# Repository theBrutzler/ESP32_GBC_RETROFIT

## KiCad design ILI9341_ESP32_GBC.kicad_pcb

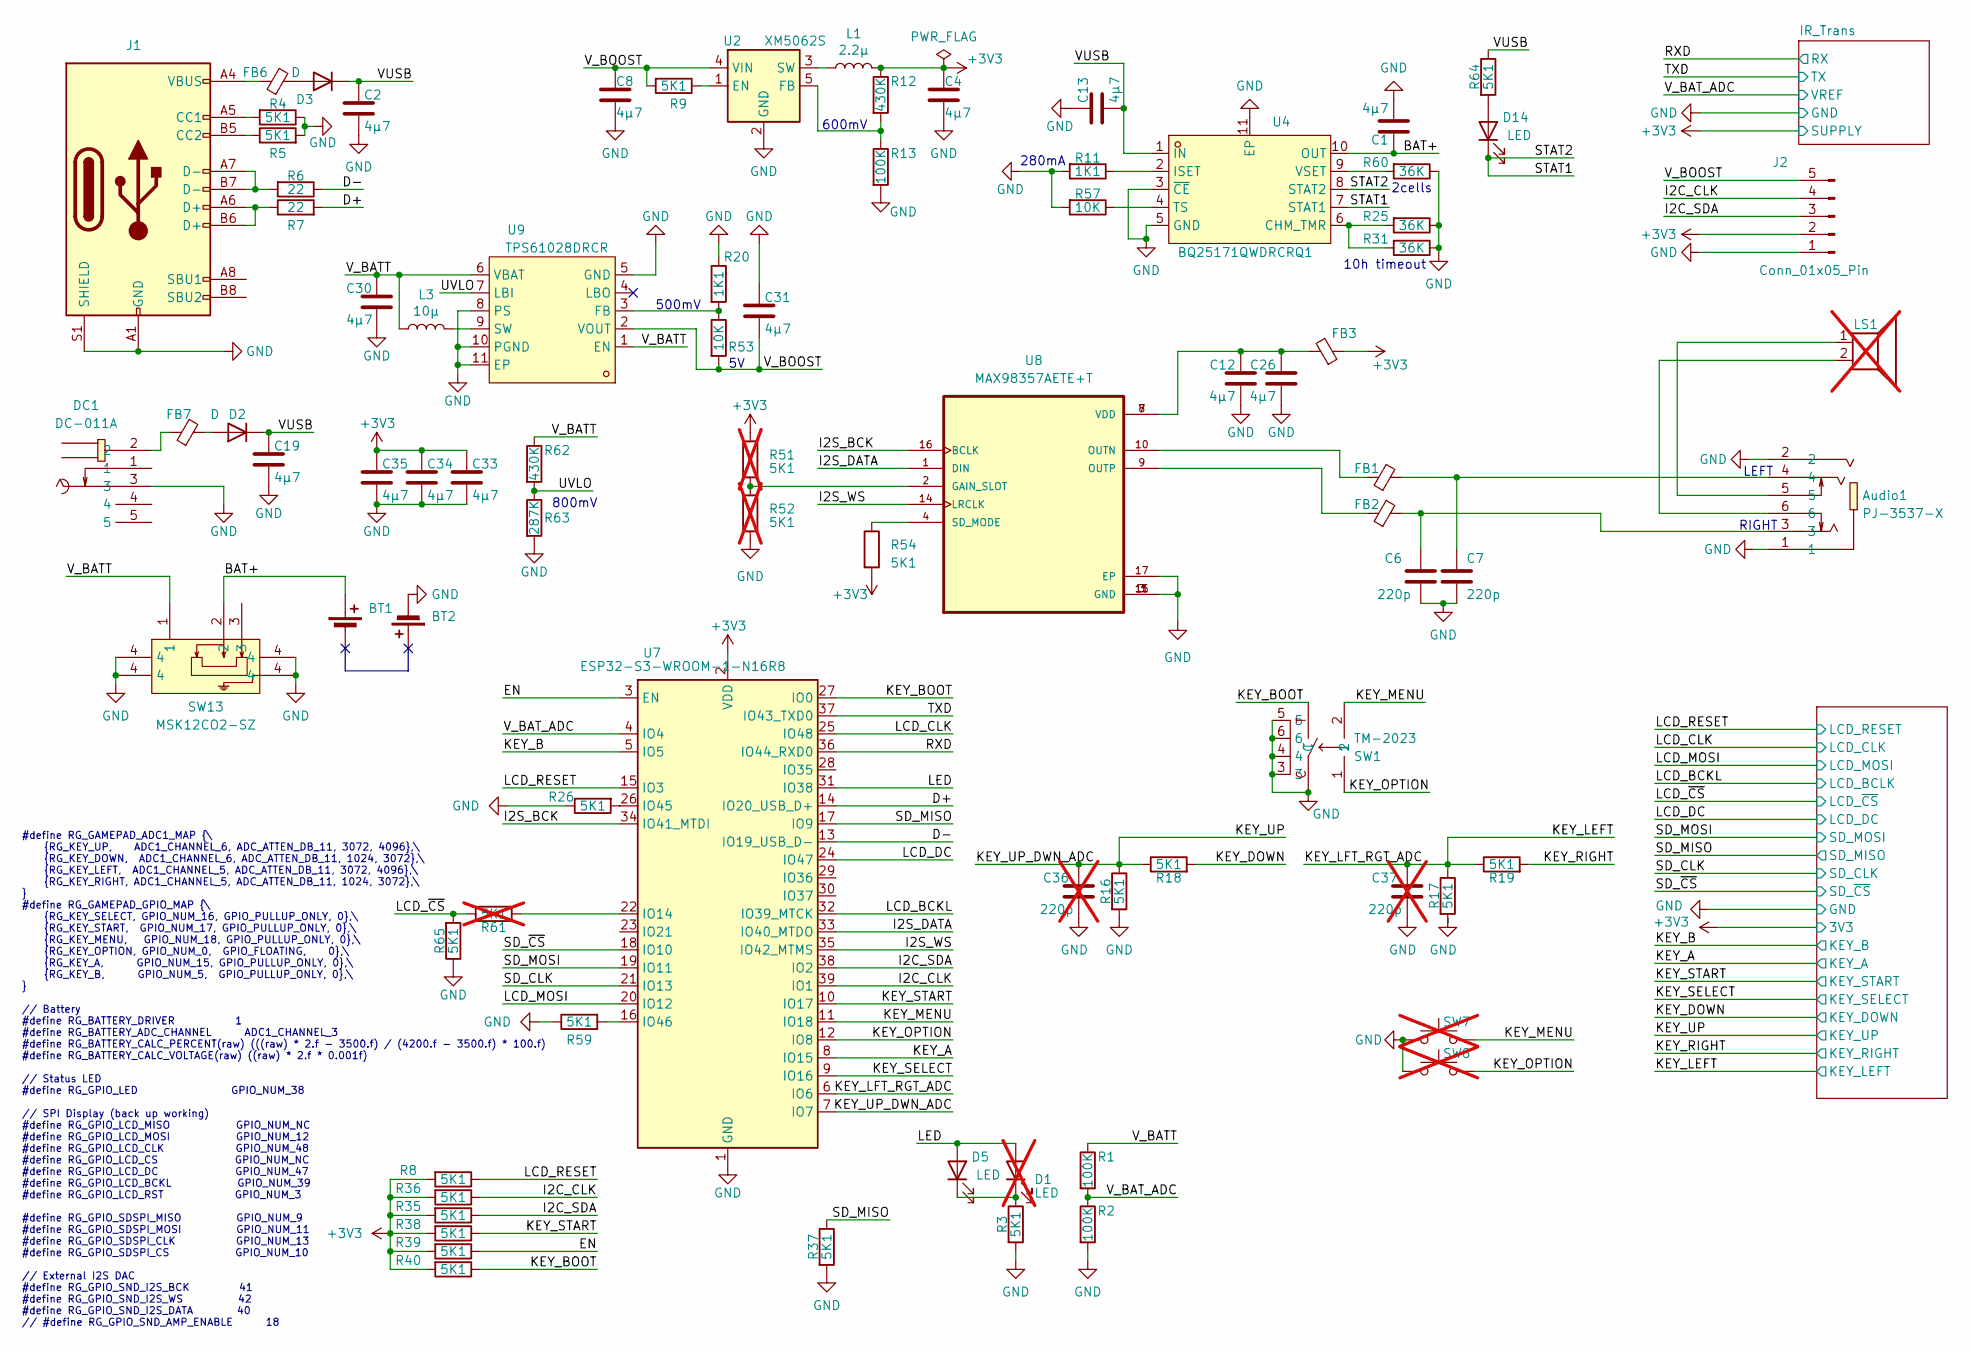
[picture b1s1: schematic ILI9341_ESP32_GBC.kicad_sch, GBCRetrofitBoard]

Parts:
Audio1: PJ-3537-X; AUDIO-SMD_PJ-3420-A-SMT_C319102; LCSC Part C319102
BT1: Battery_Cell; CONN-SMD_MY-ZJ-3030; LCSC C964874
BT2: Battery_Cell; BAT-SMD_MY-FJ-3031; LCSC C964876
C1, C2, C4, C8, C12, C13, C19, C26, C30, C31, C33, C34, C35: 4µ7; C_0603_1608Metric; LCSC C69335
C6, C7: 220p; C_0603_1608Metric; LCSC C107081
C36, C37: 220p; C_0603_1608Metric; LCSC C107081; not fitted
D1: LED; LED_D3.0mm_FlatTop; LCSC C440523; not fitted
D2, D3: D; Nexperia_CFP3_SOD-123W; LCSC C5120763
D5, D14: LED; LED_0603_1608Metric; LCSC C7496818
DC1: DC-011A; DC-IN-TH_DC-011A; LCSC Part C480366
FB1, FB2, FB3, FB6, FB7: FerriteBead_Small; L_0805_2012Metric; LCSC C963878
J1: USB_C_Receptacle_USB2.0_16P; USB_C_Receptacle_HRO_TYPE-C-31-M-12; LCSC C165948
J2: Conn_01x05_Pin; PinHeader_1x05_P2.54mm_Vertical
L1: 2.2µ; L_1210_3225Metric_Pad1.42x2.65mm_HandSolder; LCSC C3002559
L3: 10µ; L_1210_3225Metric_Pad1.42x2.65mm_HandSolder; LCSC C39846645
LS1: Speaker; PinHeader_1x02_P2.54mm_Vertical; LCSC C391015; not fitted
R1, R2, R13: 100K; R_0603_1608Metric; LCSC C15458
R3, R4, R5, R8, R9, R16, R17, R18, R19, R26, R35, R36, R37, R38, R39, R40, R54, R59, R64, R65: 5K1; R_0603_1608Metric; LCSC C26000
R6, R7: 22; R_0603_1608Metric; LCSC C1203
R11, R20: 1K1; R_0603_1608Metric; LCSC C2906975
R12, R62: 430K; R_0603_1608Metric; LCSC C25969
R25, R31, R60: 36K; R_0603_1608Metric; LCSC C23147
R51, R52, R61: 5K1; R_0603_1608Metric; LCSC C26000; not fitted
R53, R57: 10K; R_0603_1608Metric; LCSC C25804
R63: 287K; R_0603_1608Metric; LCSC C22972
SW1: TM-2023; SW-SMD_TM-2023-1; LCSC C318951
SW7, SW8: SW_Push; RubberpadButton_250µ_250µ; not fitted
SW13: MSK12CO2-SZ; SW-TH_MSK12C02; LCSC C2681568
U2: XM5062S; SOT-23-5; LCSC C2924930
U4: BQ25171QWDRCRQ1; VSON-10_L3.0-W3.0-P0.50-BL-EP1.65; LCSC Part C2861221
U7: ESP32-S3-WROOM-1-N16R8; ESP32-S3-WROOM-1; LCSC C2913202
U8: MAX98357AETE+T; QFN-16-1EP_3x3mm_P0.5mm_EP1.45x1.45mm; LCSC C910544
U9: TPS61028DRCR; VSON-10_L3.0-W3.0-P0.50-TL-EP-1; LCSC Part C575574

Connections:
+3V3: C4.1, C33.1, C34.1, C35.1, FB3.1, J2.2, L1.2, R8.2, R12.1, R35.2, R36.2, R38.2, R39.2, R40.2, R51.1, R54.2, U7.2 (VDD); also elsewhere on the board
/BAT+: BT1.1 (+), C1.1, SW13.2, U4.10 (OUT)
/D+: R7.2, U7.14 (IO20_USB_D+)
/D-: R6.1, U7.13 (IO19_USB_D-)
/EN: R39.1, U7.3 (EN)
/I2C_CLK: J2.4, R36.1, U7.39 (IO1)
/I2C_SDA: J2.3, R35.1, U7.38 (IO2)
/I2S_BCK: U7.34 (IO41_MTDI), U8.16 (BCLK)
/I2S_DATA: U7.33 (IO40_MTDO), U8.1 (DIN)
/I2S_WS: U7.35 (IO42_MTMS), U8.14 (LRCLK)
/KEY_A: U7.8 (IO15); also elsewhere on the board
/KEY_B: U7.5 (IO5); also elsewhere on the board
/KEY_BOOT: R40.1, SW1.T, U7.27 (IO0)
/KEY_DOWN: R18.2; also elsewhere on the board
/KEY_LEFT: C37.1, R17.1, R19.1, U7.6 (IO6); also elsewhere on the board
/KEY_MENU: SW1.2, SW7.2, U7.11 (IO18)
/KEY_OPTION: SW1.1, SW8.2, U7.12 (IO8)
/KEY_RIGHT: R19.2; also elsewhere on the board
/KEY_SELECT: U7.9 (IO16); also elsewhere on the board
/KEY_START: R38.1, U7.10 (IO17); also elsewhere on the board
/KEY_UP: C36.1, R16.1, R18.1, U7.7 (IO7); also elsewhere on the board
/LCD_BCKL: U7.32 (IO39_MTCK); also elsewhere on the board
/LCD_CLK: U7.25 (IO48); also elsewhere on the board
/LCD_DC: U7.24 (IO47); also elsewhere on the board
/LCD_MOSI: U7.20 (IO12); also elsewhere on the board
/LCD_RESET: R8.1, U7.15 (IO3); also elsewhere on the board
/LCD_~CS: R61.2, R65.2; also elsewhere on the board
/LED: D1.2 (A), D5.2 (A), U7.31 (IO38)
/RXD: U7.36 (IO44_RXD0); also elsewhere on the board
/SD_CLK: U7.21 (IO13); also elsewhere on the board
/SD_MISO: R37.1, U7.17 (IO9); also elsewhere on the board
/SD_MOSI: U7.19 (IO11); also elsewhere on the board
/SD_~CS: U7.18 (IO10); also elsewhere on the board
/STAT1: D14.1 (K), U4.7 (STAT1), U4.8 (STAT2)
/TXD: U7.37 (IO43_TXD0); also elsewhere on the board
/UVLO: R62.2, R63.1, U9.7 (LBI)
/VUSB: C2.1, C13.2, C19.1, D2.1 (K), D3.1 (K), R64.1, U4.1 (IN)
/V_BATT: C30.1, L3.1, R1.1, R62.1, SW13.1, U9.1 (EN), U9.6 (VBAT)
/V_BAT_ADC: R1.2, R2.1, U7.4 (IO4); also elsewhere on the board
/V_BOOST: C8.1, C31.2, J2.5, R9.2, R53.2, U2.4 (VIN), U9.2 (VOUT)
GND: Audio1.1, Audio1.2, BT2.2 (-), C1.2, C2.2, C4.2, C6.2, C7.1, C8.2, C12.2, C13.1, C19.2, C26.2, C30.2, C31.1, C33.2, C34.2, C35.2, C36.2, C37.2, DC1.3, J1.A1 (GND), J1.A12 (GND), J1.B1 (GND), J1.B12 (GND), J1.S1 (SHIELD), J2.1, R2.2, R3.2, R4.1, R5.2, R11.2, R13.2, R16.2, R17.2, R20.1, R25.1, R26.1, R31.1, R37.2, R52.2, R57.2, R59.1, R60.1, R63.2, R65.1, SW1.3, SW1.4, SW1.5, SW1.6, SW1.C, SW7.1, SW8.1, SW13.4, U2.2 (GND), U4.3 (~CE), U4.5 (GND), U4.11 (EP), U7.1 (GND), U7.40 (GND), U7.41 (GND), U8.3 (GND), U8.11 (GND), U8.15 (GND), U8.17 (EP), U9.5 (GND), U9.8 (PS), U9.10 (PGND), U9.11 (EP); also elsewhere on the board
unnamed: Audio1.3, C6.1, FB2.2
unnamed: Audio1.4, C7.2, FB1.2
unnamed: Audio1.5, LS1.1
unnamed: Audio1.6, LS1.2
unnamed: C12.1, C26.1, FB3.2, U8.7 (VDD), U8.8 (VDD)
unnamed: D1.1 (K), D5.1 (K), R3.1
unnamed: D2.2 (A), FB7.2
unnamed: D3.2 (A), FB6.2
unnamed: D14.2 (A), R64.2
unnamed: DC1.2, FB7.1
unnamed: FB6.1, J1.A4 (VBUS), J1.A9 (VBUS), J1.B4 (VBUS), J1.B9 (VBUS)
unnamed: J1.A5 (CC1), R4.2
unnamed: J1.B5 (CC2), R5.1
unnamed: J1.A6 (D+), J1.B6 (D+), R7.1
unnamed: J1.A7 (D-), J1.B7 (D-), R6.2
unnamed: R9.1, U2.1 (EN)
unnamed: R12.2, R13.1, U2.5 (FB)
unnamed: L1.1, U2.3 (SW)
unnamed: R25.2, R31.2, U4.6 (CHM_TMR)
unnamed: R11.1, U4.2 (ISET)
unnamed: R57.1, U4.4 (TS)
unnamed: R60.2, U4.9 (VSET)
unnamed: R61.1, U7.22 (IO14)
unnamed: R26.2, U7.26 (IO45)
unnamed: R59.2, U7.16 (IO46)
unnamed: R51.2, R52.1, U8.2 (GAIN_SLOT)
unnamed: FB1.1, U8.10 (OUTN)
unnamed: FB2.1, U8.9 (OUTP)
unnamed: R54.1, U8.4 (SD_MODE)
unnamed: R20.2, R53.1, U9.3 (FB)
unnamed: L3.2, U9.9 (SW)

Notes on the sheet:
RIGHT
500mV
600mV
280mA
2cells
LEFT
800mV
#define RG_GAMEPAD_ADC1_MAP {\ {RG_KEY_UP, ADC1_CHANNEL_6, ADC_ATTEN_DB_11, 3072, 4096},\ {RG_KEY_DOWN, ADC1_CHANNEL_6, ADC_ATTEN_DB_11, 1024, 3072},\ {RG_KEY_LEFT, ADC1_CHANNEL_5, ADC_ATTEN_DB_11, 3072, 4096},\ {RG_KEY_RIGHT, ADC1_CHANNEL_5, ADC_ATTEN_DB_11, 1024, 3072},\ } #define RG_GAMEPAD_GPIO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
10h timeout

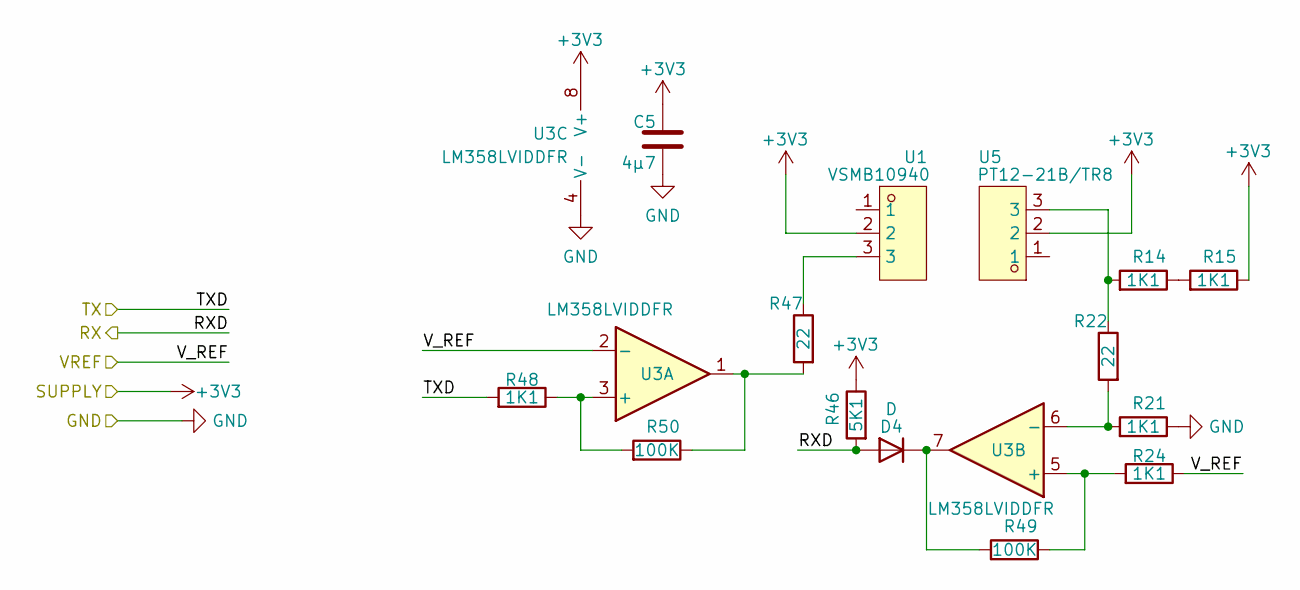
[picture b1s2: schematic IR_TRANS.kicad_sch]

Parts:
C5: 4µ7; C_0603_1608Metric; LCSC C69335
D4: D; Nexperia_CFP3_SOD-123W; LCSC C5120763
R14, R15, R21, R24, R48: 1K1; R_0603_1608Metric; LCSC C2906975
R22, R47: 22; R_0603_1608Metric; LCSC C1203
R46: 5K1; R_0603_1608Metric; LCSC C26000
R49, R50: 100K; R_0603_1608Metric; LCSC C15458
U1: VSMB10940; LED-SMD_3P-L3.0-W1.0-FD; LCSC Part C4749241
U3: LM358LVIDDFR; TSOT-23-8; LCSC C1849428
U5: PT12-21B/TR8; LED-SMD_3P-L3.0-W1.0-FD; LCSC C264383

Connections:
+3V3: C5.1, R15.1, R46.1, U1.2, U3.8 (V+), U5.2; also elsewhere on the board
/RXD: D4.2 (A), R46.2; also elsewhere on the board
/TXD: R48.2; also elsewhere on the board
/V_BAT_ADC: R24.1, U3.2 (-); also elsewhere on the board
GND: C5.2, R21.1, U3.4 (V-); also elsewhere on the board
unnamed: D4.1 (K), R49.2, U3.7
unnamed: R14.1, R15.2
unnamed: R14.2, R22.1, U5.3
unnamed: R47.1, U1.3
unnamed: R47.2, R50.1, U3.1
unnamed: R48.1, R50.2, U3.3 (+)
unnamed: R24.2, R49.1, U3.5 (+)
unnamed: R21.2, R22.2, U3.6 (-)

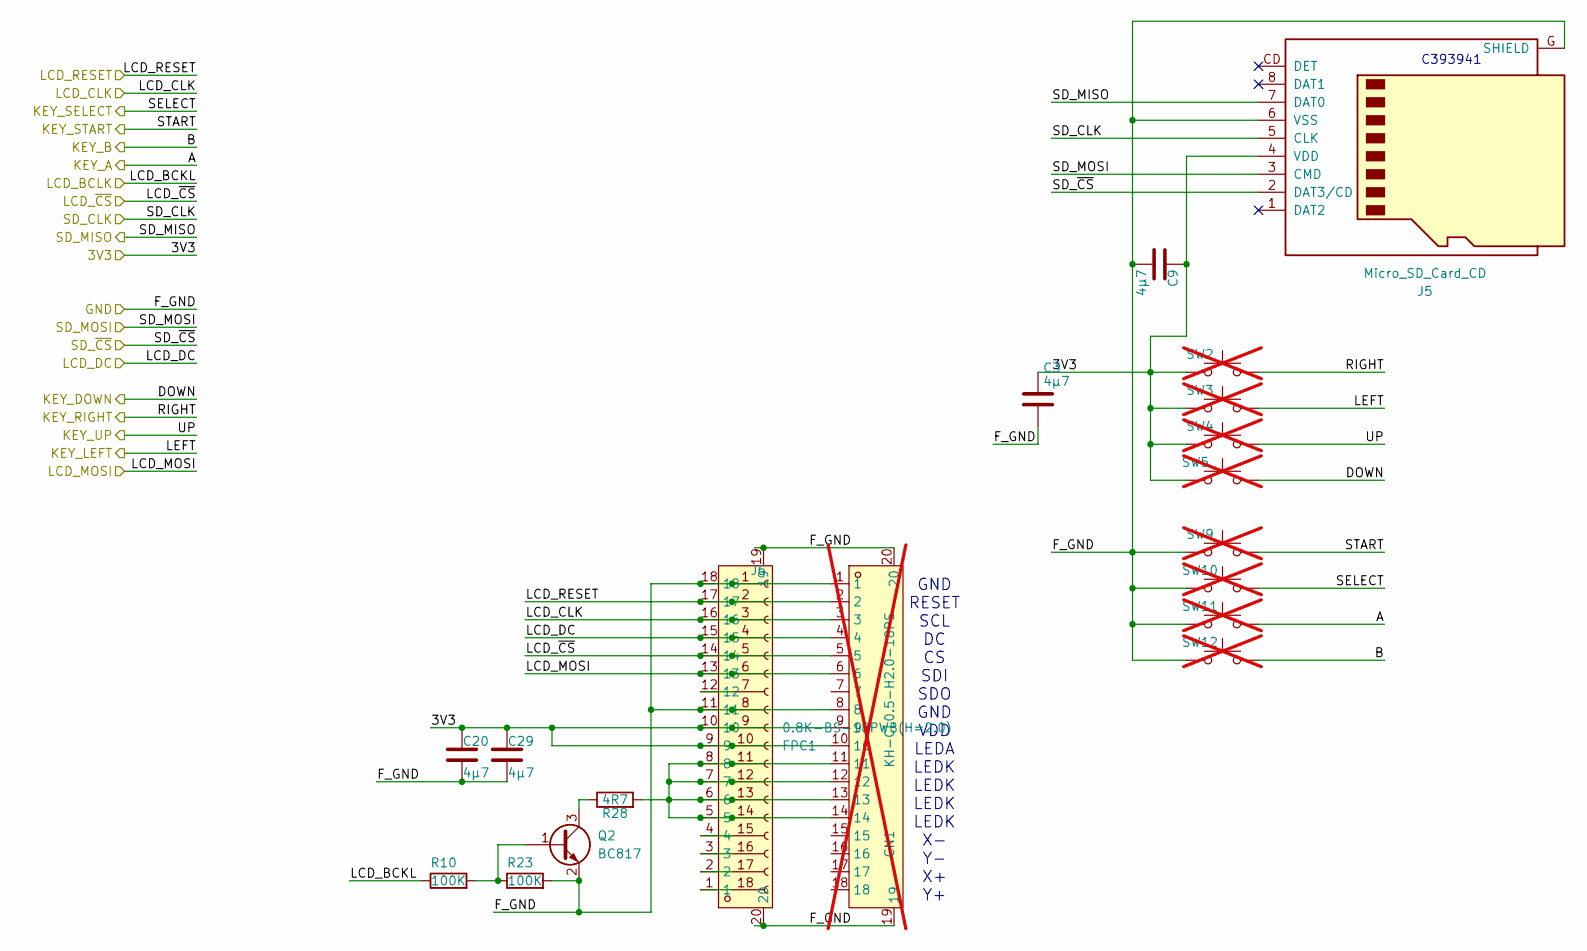
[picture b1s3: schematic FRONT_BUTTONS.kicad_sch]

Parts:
C3, C9, C20, C29: 4µ7; C_0603_1608Metric; LCSC C69335
CN1: KH-CL0.5-H2.0-18PS; FPC-SMD_KH-CL0.5-H2.0-18PS; LCSC Part C2828051; not fitted
FPC1: 0.8K-BS-18PWB(H=2.0); FPC-SMD_18P-P0.80_HDGC_0.8K-BS-18PWB; LCSC Part C2915417
J5: Micro_SD_Card_CD; MicroSD_Self_ bomb; LCSC C393941
J6: Conn_01x18_Socket; solder connector 0.8mm 18 pin
Q2: BC817; SOT-323_SC-70; LCSC C605312
R10, R23: 100K; R_0603_1608Metric; LCSC C15458
R28: 4R7; R_0603_1608Metric; LCSC C491192
SW2, SW3, SW4, SW5: SW_Push; RubberpadButton_GBC_CROSS; not fitted
SW9, SW10, SW11, SW12: SW_Push; RubberpadButton_250µ_250µ; not fitted

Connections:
+3V3: C3.1, C9.1, C20.1, C29.1, CN1.9, CN1.10, FPC1.9, FPC1.10, J5.4 (VDD), J6.9, J6.10, SW2.1, SW3.1, SW4.1, SW5.2; also elsewhere on the board
/KEY_A: SW11.2; also elsewhere on the board
/KEY_B: SW12.2; also elsewhere on the board
/KEY_DOWN: SW5.1; also elsewhere on the board
/KEY_LEFT: SW3.2; also elsewhere on the board
/KEY_RIGHT: SW2.2; also elsewhere on the board
/KEY_SELECT: SW10.2; also elsewhere on the board
/KEY_START: SW9.2; also elsewhere on the board
/KEY_UP: SW4.2; also elsewhere on the board
/LCD_BCKL: R10.1; also elsewhere on the board
/LCD_CLK: CN1.3, FPC1.16, J6.3; also elsewhere on the board
/LCD_DC: CN1.4, FPC1.15, J6.4; also elsewhere on the board
/LCD_MOSI: CN1.6, FPC1.13, J6.6; also elsewhere on the board
/LCD_RESET: CN1.2, FPC1.17, J6.2; also elsewhere on the board
/LCD_~CS: CN1.5, FPC1.14, J6.5; also elsewhere on the board
/SD_CLK: J5.5 (CLK); also elsewhere on the board
/SD_MISO: J5.7 (DAT0); also elsewhere on the board
/SD_MOSI: J5.3 (CMD); also elsewhere on the board
/SD_~CS: J5.2 (DAT3/CD); also elsewhere on the board
GND: C3.2, C9.2, C20.2, C29.2, CN1.1, CN1.8, CN1.19, CN1.20, FPC1.11, FPC1.18, FPC1.19, FPC1.20, J5.6 (VSS), J5.G (SHIELD), J6.1, J6.8, Q2.2 (E), R23.2, SW9.1, SW10.1, SW11.1, SW12.1; also elsewhere on the board
unnamed: FPC1.12, J6.7
unnamed: CN1.11, CN1.12, CN1.13, CN1.14, FPC1.5, FPC1.6, FPC1.7, FPC1.8, J6.11, J6.12, J6.13, J6.14, R28.2
unnamed: FPC1.4, J6.15
unnamed: FPC1.3, J6.16
unnamed: FPC1.2, J6.17
unnamed: FPC1.1, J6.18
unnamed: Q2.1 (B), R10.2, R23.1
unnamed: Q2.3 (C), R28.1

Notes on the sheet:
GND RESET SCL DC CS SDI SDO GND VDD LEDA LEDK LEDK LEDK LEDK X- Y- X+ Y+
C393941

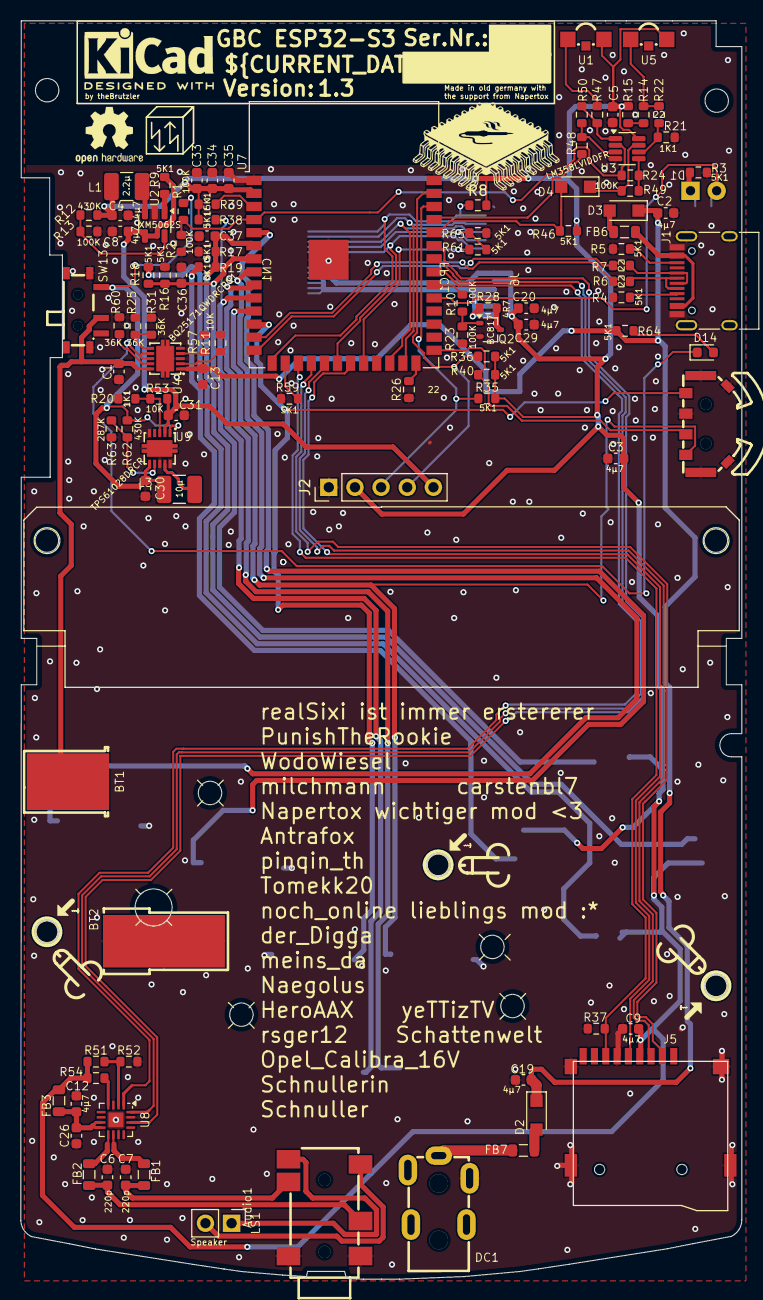
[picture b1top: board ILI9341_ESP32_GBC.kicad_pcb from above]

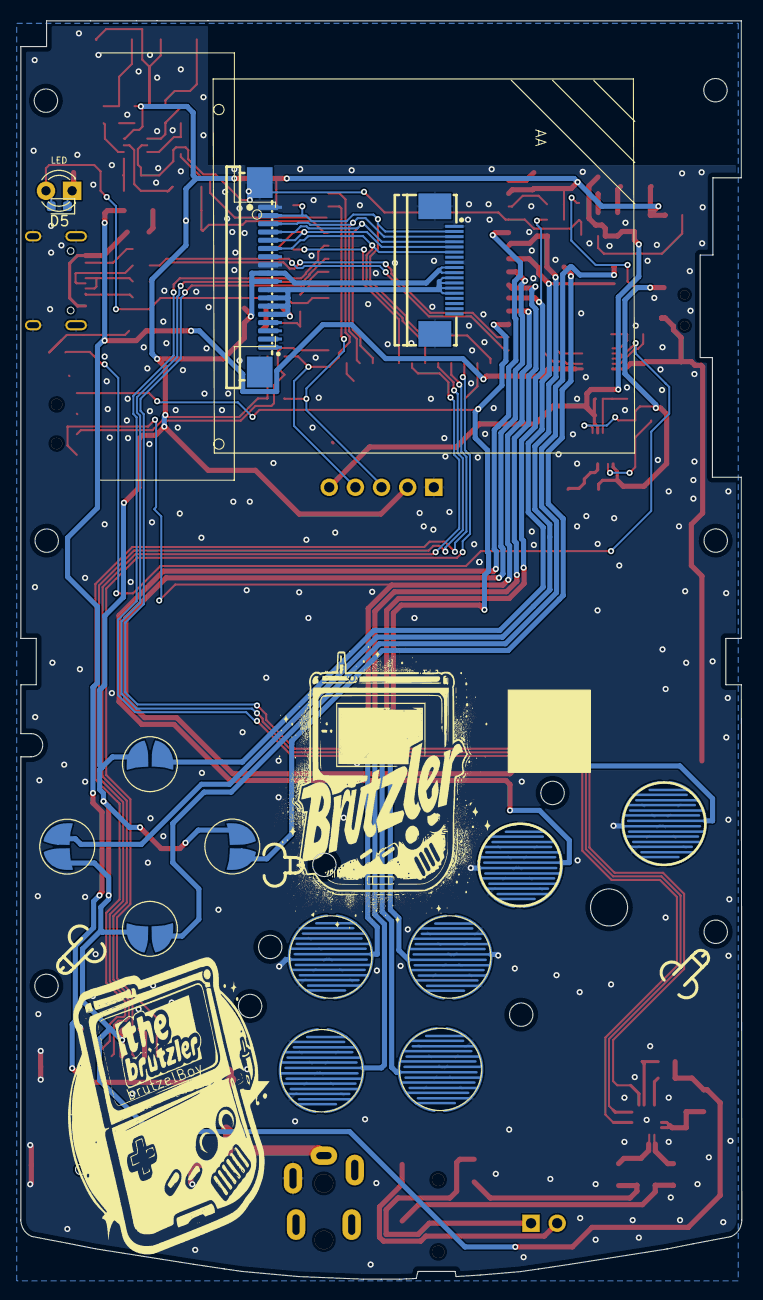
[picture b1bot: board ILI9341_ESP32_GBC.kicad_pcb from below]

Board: 2 copper layers, 70.0 x 122.2 mm, 119 parts (15 on the bottom side), 88 nets.

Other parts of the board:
SM3: SYM_Arrow45_Tiny; Symbol_kurzschlussblog

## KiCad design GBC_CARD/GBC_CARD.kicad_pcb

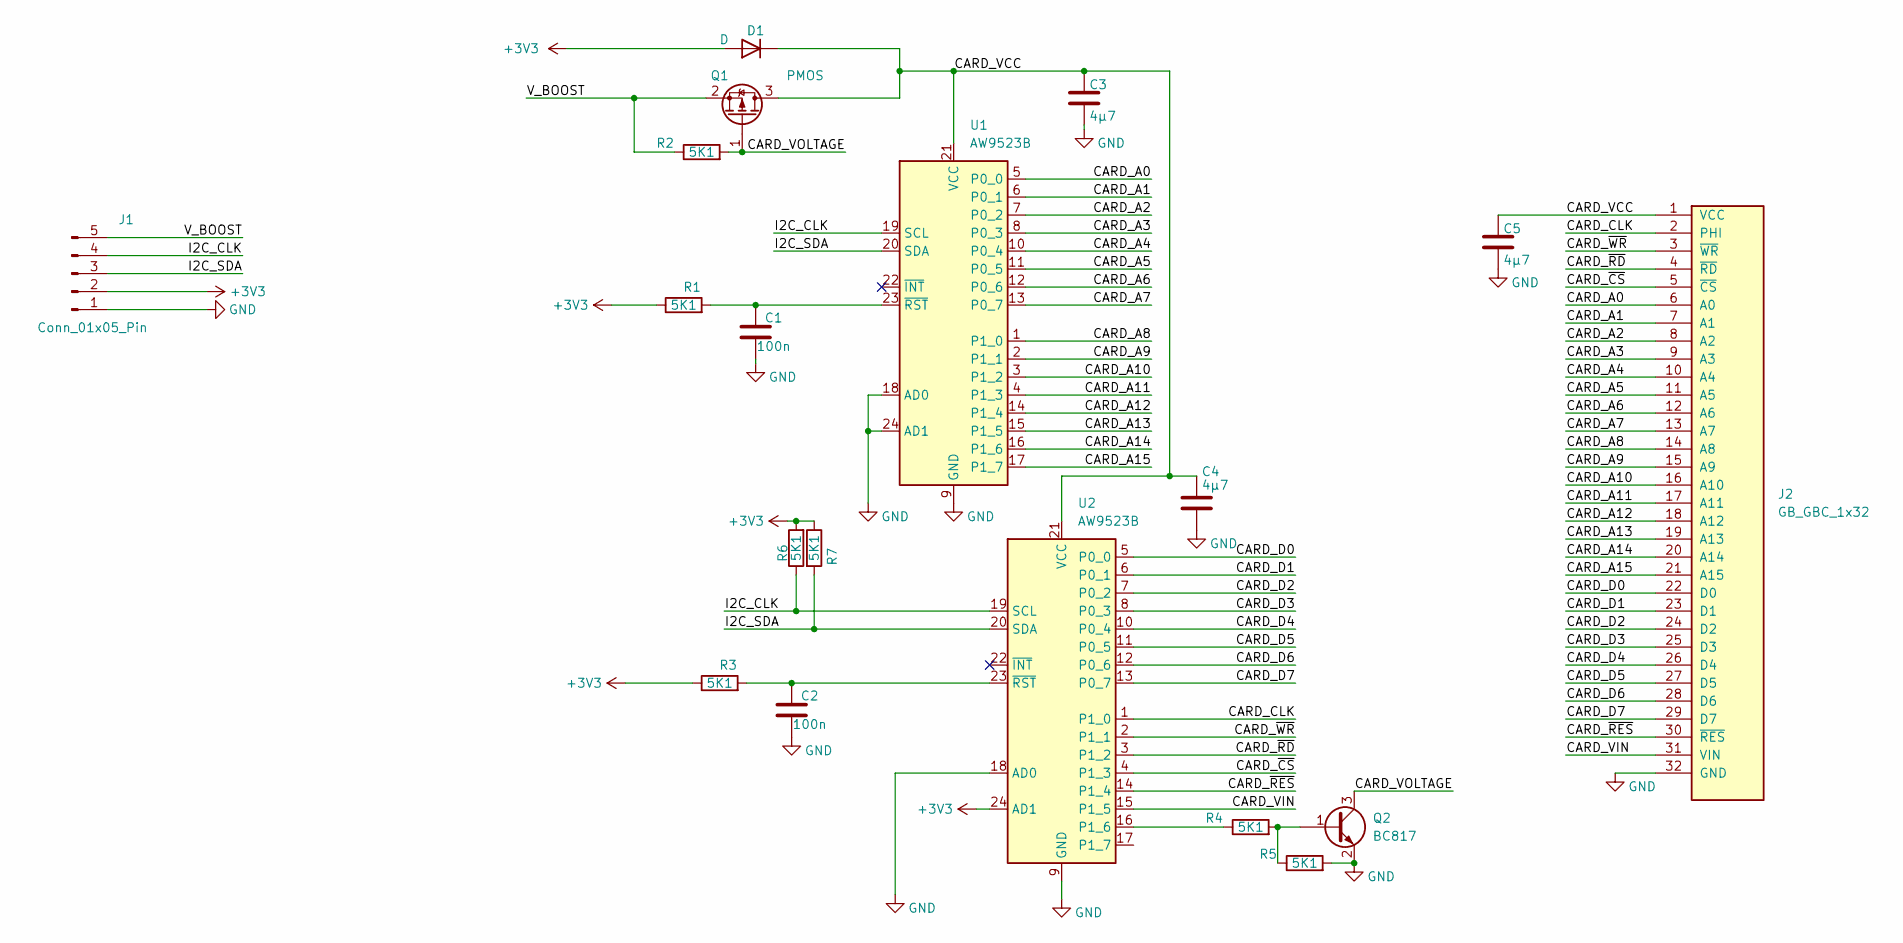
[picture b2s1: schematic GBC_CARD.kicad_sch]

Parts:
C1, C2: 100n; C_0603_1608Metric; LCSC C30926
C3, C4, C5: 4µ7; C_0603_1608Metric; LCSC C69335
D1: D; Nexperia_CFP3_SOD-123W; LCSC C5120763
J1: Conn_01x05_Pin; PinHeader_1x05_P2.54mm_Vertical
J2: GB_GBC_1x32
Q1: PMOS; SOT-323_SC-70; LCSC C19078062
Q2: BC817; SOT-323_SC-70; LCSC C605312
R1, R2, R3, R4, R5, R6, R7: 5K1; R_0603_1608Metric; LCSC C26000
U1, U2: AW9523B; QFN-24-1EP_4x4mm_P0.5mm_EP2.7x2.7mm; LCSC C148077

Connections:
+3V3: D1.2 (A), J1.2, R1.1, R3.1, R6.2, R7.1, U2.24 (AD1)
/CARD_A0: J2.6 (A0), U1.5 (P0_0)
/CARD_A1: J2.7 (A1), U1.6 (P0_1)
/CARD_A2: J2.8 (A2), U1.7 (P0_2)
/CARD_A3: J2.9 (A3), U1.8 (P0_3)
/CARD_A4: J2.10 (A4), U1.10 (P0_4)
/CARD_A5: J2.11 (A5), U1.11 (P0_5)
/CARD_A6: J2.12 (A6), U1.12 (P0_6)
/CARD_A7: J2.13 (A7), U1.13 (P0_7)
/CARD_A8: J2.14 (A8), U1.1 (P1_0)
/CARD_A9: J2.15 (A9), U1.2 (P1_1)
/CARD_A10: J2.16 (A10), U1.3 (P1_2)
/CARD_A11: J2.17 (A11), U1.4 (P1_3)
/CARD_A12: J2.18 (A12), U1.14 (P1_4)
/CARD_A13: J2.19 (A13), U1.15 (P1_5)
/CARD_A14: J2.20 (A14), U1.16 (P1_6)
/CARD_A15: J2.21 (A15), U1.17 (P1_7)
/CARD_CLK: J2.2 (PHI), U2.1 (P1_0)
/CARD_D0: J2.22 (D0), U2.5 (P0_0)
/CARD_D1: J2.23 (D1), U2.6 (P0_1)
/CARD_D2: J2.24 (D2), U2.7 (P0_2)
/CARD_D3: J2.25 (D3), U2.8 (P0_3)
/CARD_D4: J2.26 (D4), U2.10 (P0_4)
/CARD_D5: J2.27 (D5), U2.11 (P0_5)
/CARD_D6: J2.28 (D6), U2.12 (P0_6)
/CARD_D7: J2.29 (D7), U2.13 (P0_7)
/CARD_VCC: C3.1, C4.1, C5.1, D1.1 (K), J2.1 (VCC), Q1.3 (D), U1.21 (VCC), U2.21 (VCC)
/CARD_VIN: J2.31 (VIN), U2.15 (P1_5)
/CARD_VOLTAGE: Q1.1 (G), Q2.3 (C), R2.2
/CARD_~CS: J2.5 (~CS), U2.4 (P1_3)
/CARD_~RD: J2.4 (~RD), U2.3 (P1_2)
/CARD_~RES: J2.30 (~RES), U2.14 (P1_4)
/CARD_~WR: J2.3 (~WR), U2.2 (P1_1)
/I2C_CLK: J1.4, R6.1, U1.19 (SCL), U2.19 (SCL)
/I2C_SDA: J1.3, R7.2, U1.20 (SDA), U2.20 (SDA)
/V_BOOST: J1.5, Q1.2 (S), R2.1
GND: C1.1, C2.1, C3.2, C4.2, C5.2, J1.1, J2.32 (GND), Q2.2 (E), R5.2, U1.9 (GND), U1.18 (AD0), U1.24 (AD1), U1.25 (GND), U2.9 (GND), U2.18 (AD0), U2.25 (GND)
unnamed: Q2.1 (B), R4.2, R5.1
unnamed: C1.2, R1.2, U1.23 (~RST)
unnamed: R4.1, U2.16 (P1_6)
unnamed: C2.2, R3.2, U2.23 (~RST)

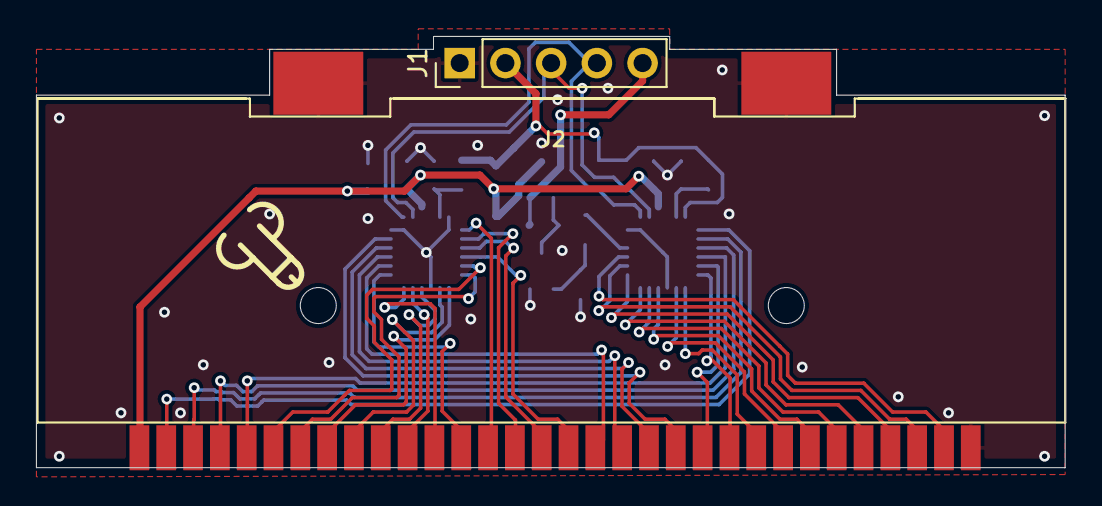
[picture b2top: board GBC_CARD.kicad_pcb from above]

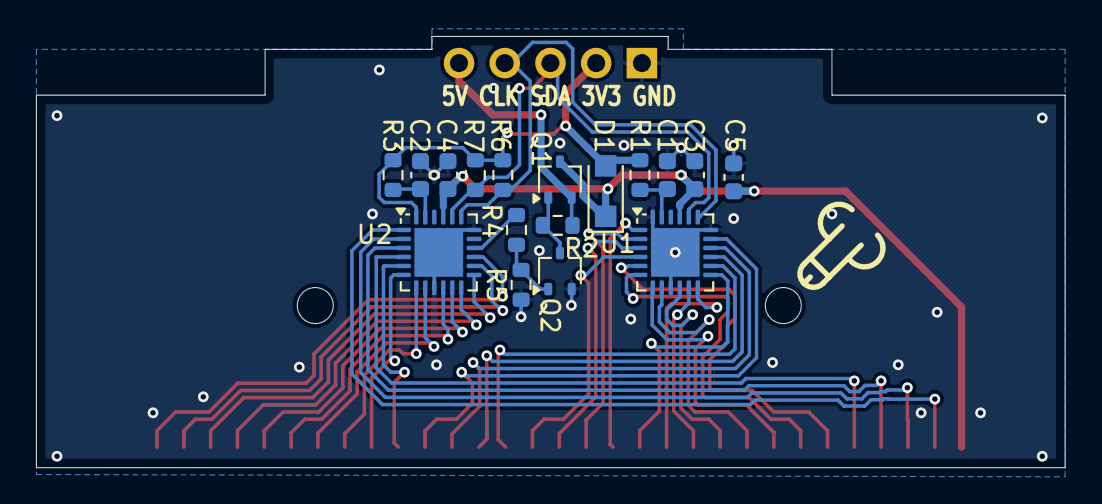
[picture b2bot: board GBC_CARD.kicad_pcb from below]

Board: 2 copper layers, 57.1 x 24.0 mm, 19 parts (17 on the bottom side), 41 nets.

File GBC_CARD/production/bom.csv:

Designator,Footprint,Quantity,Value,LCSC Part #
"C1, C2",0603,2,100n,C30926
"C3, C4, C5",0603,3,4µ7,C69335
D1,Nexperia_CFP3_SOD-123W,1,D,C5120763
J1,PinHeader_1x05_P2.54mm_Vertical,1,Conn_01x05_Pin,
J2,GB_GBC_1x32,1,GB_GBC_1x32,
Q1,SOT-323_SC-70,1,PMOS,C19078062
Q2,SOT-323_SC-70,1,BC817,C605312
"R1, R2, R3, R4, R5, R6, R7",0603,7,5K1,C26000
"U1, U2",QFN-24-1EP_4x4mm_P0.5mm_EP2.7x2.7mm,2,AW9523B,C148077

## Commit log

2024-08-06 Initial upload (untested version)
2024-08-06 add 3d render and model
2024-09-03 update online version before change to esp32 s3
2024-09-03 updated version with esp32 s3 and i2s audio ic
2024-10-29 initial software upload
    NOT WORKING AT THE MOMENT
2024-11-14 Order V1
2024-11-14 update carstenbl7 in silkscreen
2024-12-27 update original flash img
2024-12-27 update pcb and upload schematic
2024-12-28 add adc testsoftware to test the directional pad
2025-01-03 upload retro-go config file
    config file for https://github.com/ducalex/retro-go source used on gbc inicial
2025-01-03 Upload order version 1.3
2025-01-09 Update Software (VBAT in ADC ino and retro.go img)
2025-01-12 update retro-go
2025-01-14 update dpad value (add filter)
2025-03-18 alte version die schneller ist
2025-03-18 update old but gold
